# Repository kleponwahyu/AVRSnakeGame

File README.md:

8-bit Snake Game with AVR!
Complete with the schematic, board design, and the program!

The board design can be implemented for other games that uses low pixel count, for including tetris, car race and many more! (but no code yet...)

Note:
- The code is in C
- The board design and schematics are in EAGLE
- Already working as intended, but the pcb still need cleaning and can be shrinked.
- The Dot Matrix is in wrong angle, so physical and logical coordinates needed, and it takes memory space and clock. Will fix this for sure!

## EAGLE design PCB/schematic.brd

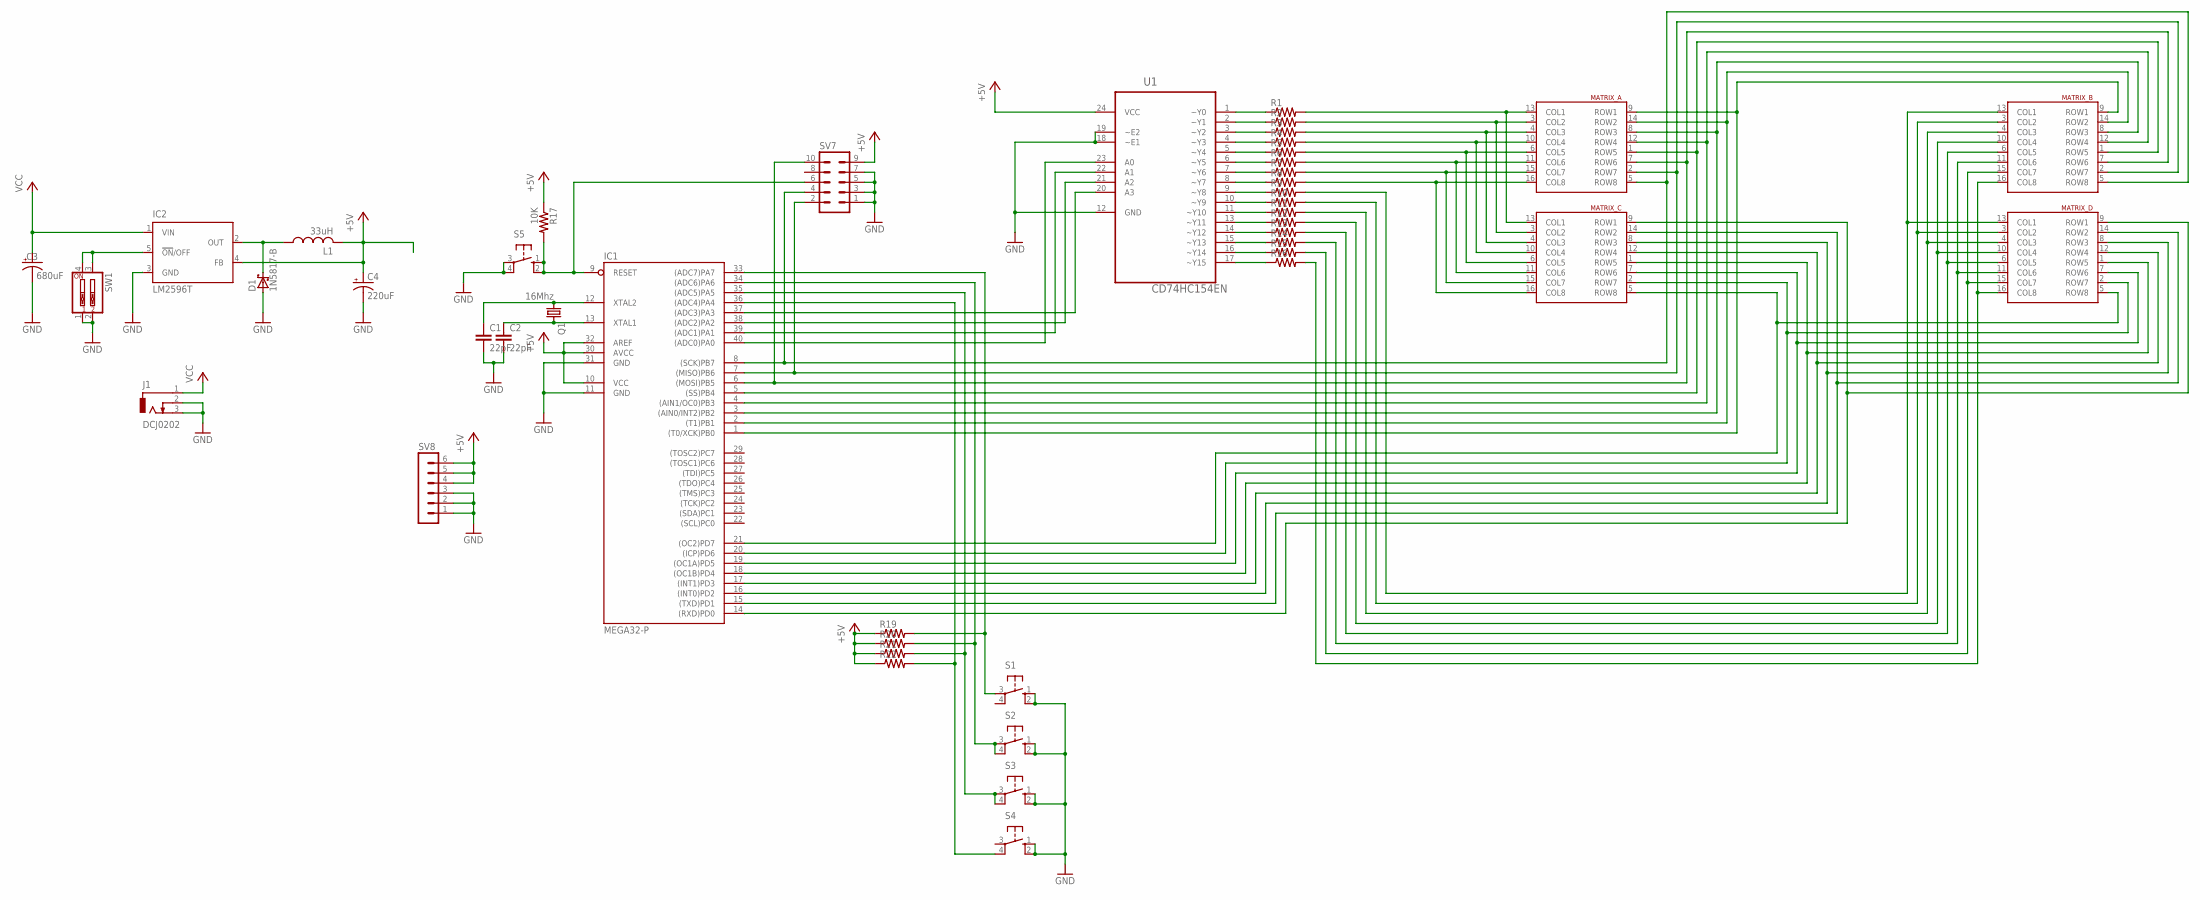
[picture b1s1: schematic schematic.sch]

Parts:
C1, C2: 22pF; C025-024X044
C3: 680uF; E3,5-8
C4: 220uF; E3,5-8
D1: 1N5817-B; DO41-7.6
IC1: MEGA32-P; DIL40
IC2: LM2596T; T05D
J1: DCJ0202
L1: 33uH; 0207/10
MATRIX_A: LED_8X8_MATRIXYGD2/A; MATRIX_8X8_38MM
MATRIX_B: LED_8X8_MATRIXYGD2/A; MATRIX_8X8_38MM
MATRIX_C: LED_8X8_MATRIXYGD2/A; MATRIX_8X8_38MM
MATRIX_D: LED_8X8_MATRIXYGD2/A; MATRIX_8X8_38MM
Q1: 16Mhz; HC49/S
R1, R2, R3, R4, R5, R6, R7, R8, R9, R10, R11, R12, R13, R14, R15, R16: R-US_0204/2V; 0204V
R17: 10K; 0204/7
R19, R20, R21, R22: R-US_0204/7; 0204/7
S1, S2, S3, S4, S5: 10-XX; B3F-10XX
SV7: MA05-2
SV8: MA06-1
SW1: SW_DIP-2; EDG-02
U1: CD74HC154EN; DIP254P762X508-24

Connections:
+5V: C4.+, IC1.10 (VCC), IC1.30 (AVCC), IC1.32 (AREF), IC2.4 (FB), L1.2, R17.1, R19.1, R20.1, R21.1, R22.1, SV7.9, SV8.4, SV8.5, SV8.6, U1.24 (VCC)
GND: C1.2, C2.2, C3.-, C4.-, D1.A, IC1.11 (GND), IC1.31 (GND), IC2.3 (GND), J1.2, J1.3, S1.1 (S), S1.2 (S1), S2.1 (S), S2.2 (S1), S3.1 (S), S3.2 (S1), S4.1 (S), S4.2 (S1), S5.3, S5.4 (P1), SV7.1, SV7.3, SV7.5, SV7.7, SV8.1, SV8.2, SV8.3, SW1.1, SW1.2, U1.12 (GND), U1.18 (~E1), U1.19 (~E2)
unnamed: R1.1, U1.1 (~Y0)
unnamed: R2.1, U1.2 (~Y1)
unnamed: R3.1, U1.3 (~Y2)
unnamed: R4.1, U1.4 (~Y3)
unnamed: R5.1, U1.5 (~Y4)
unnamed: R6.1, U1.6 (~Y5)
unnamed: R7.1, U1.7 (~Y6)
unnamed: R8.1, U1.8 (~Y7)
unnamed: R9.1, U1.9 (~Y8)
unnamed: R10.1, U1.10 (~Y9)
unnamed: R11.1, U1.11 (~Y10)
unnamed: R12.1, U1.13 (~Y11)
unnamed: R13.1, U1.14 (~Y12)
unnamed: R14.1, U1.15 (~Y13)
unnamed: R15.1, U1.16 (~Y14)
unnamed: R16.1, U1.17 (~Y15)
unnamed: MATRIX_A.13 (COL1), MATRIX_C.13 (COL1), R1.2
unnamed: MATRIX_A.3 (COL2), MATRIX_C.3 (COL2), R2.2
unnamed: MATRIX_A.4 (COL3), MATRIX_C.4 (COL3), R3.2
unnamed: MATRIX_A.10 (COL4), MATRIX_C.10 (COL4), R4.2
unnamed: MATRIX_A.6 (COL5), MATRIX_C.6 (COL5), R5.2
unnamed: MATRIX_A.11 (COL6), MATRIX_C.11 (COL6), R6.2
unnamed: MATRIX_A.15 (COL7), MATRIX_C.15 (COL7), R7.2
unnamed: MATRIX_A.16 (COL8), MATRIX_C.16 (COL8), R8.2
unnamed: IC1.7 ((MISO)PB6), MATRIX_A.2 (ROW7), MATRIX_B.2 (ROW7), SV7.2
unnamed: IC1.8 ((SCK)PB7), MATRIX_A.5 (ROW8), MATRIX_B.5 (ROW8), SV7.4
unnamed: IC1.5 ((SS)PB4), MATRIX_A.1 (ROW5), MATRIX_B.1 (ROW5)
unnamed: IC1.3 ((AIN0/INT2)PB2), MATRIX_A.8 (ROW3), MATRIX_B.8 (ROW3)
unnamed: IC1.1 ((T0/XCK)PB0), MATRIX_A.9 (ROW1), MATRIX_B.9 (ROW1)
unnamed: IC1.15 ((TXD)PD1), MATRIX_C.14 (ROW2), MATRIX_D.14 (ROW2)
unnamed: IC1.17 ((INT1)PD3), MATRIX_C.12 (ROW4), MATRIX_D.12 (ROW4)
unnamed: IC1.20 ((ICP)PD6), MATRIX_C.2 (ROW7), MATRIX_D.2 (ROW7)
unnamed: IC1.9 (RESET), R17.2, S5.1 (S), S5.2 (S1), SV7.6
unnamed: MATRIX_B.15 (COL7), MATRIX_D.15 (COL7), R15.2
unnamed: C2.1, IC1.13 (XTAL1), Q1.2
unnamed: MATRIX_B.6 (COL5), MATRIX_D.6 (COL5), R13.2
unnamed: C1.1, IC1.12 (XTAL2), Q1.1
unnamed: MATRIX_B.4 (COL3), MATRIX_D.4 (COL3), R11.2
unnamed: MATRIX_B.13 (COL1), MATRIX_D.13 (COL1), R9.2
unnamed: IC1.39 ((ADC1)PA1), U1.22 (A1)
unnamed: IC1.37 ((ADC3)PA3), U1.20 (A3)
unnamed: IC1.34 ((ADC6)PA6), R20.2, S2.3, S2.4 (P1)
unnamed: IC1.36 ((ADC4)PA4), R22.2, S4.4 (P1)
unnamed: MATRIX_B.3 (COL2), MATRIX_D.3 (COL2), R10.2
unnamed: IC1.2 ((T1)PB1), MATRIX_A.14 (ROW2), MATRIX_B.14 (ROW2)
unnamed: MATRIX_B.10 (COL4), MATRIX_D.10 (COL4), R12.2
unnamed: MATRIX_B.11 (COL6), MATRIX_D.11 (COL6), R14.2
unnamed: IC1.4 ((AIN1/OC0)PB3), MATRIX_A.12 (ROW4), MATRIX_B.12 (ROW4)
unnamed: MATRIX_B.16 (COL8), MATRIX_D.16 (COL8), R16.2
unnamed: IC1.6 ((MOSI)PB5), MATRIX_A.7 (ROW6), MATRIX_B.7 (ROW6), SV7.10
unnamed: IC1.14 ((RXD)PD0), MATRIX_C.9 (ROW1), MATRIX_D.9 (ROW1)
unnamed: IC1.16 ((INT0)PD2), MATRIX_C.8 (ROW3), MATRIX_D.8 (ROW3)
unnamed: IC1.18 ((OC1B)PD4), MATRIX_C.1 (ROW5), MATRIX_D.1 (ROW5)
unnamed: IC1.19 ((OC1A)PD5), MATRIX_C.7 (ROW6), MATRIX_D.7 (ROW6)
unnamed: IC1.21 ((OC2)PD7), MATRIX_C.5 (ROW8), MATRIX_D.5 (ROW8)
unnamed: IC1.35 ((ADC5)PA5), R21.2, S3.3, S3.4 (P1)
unnamed: IC1.33 ((ADC7)PA7), R19.2, S1.3
unnamed: IC1.40 ((ADC0)PA0), U1.23 (A0)
unnamed: IC1.38 ((ADC2)PA2), U1.21 (A2)
unnamed: D1.C, IC2.2 (OUT), L1.1
unnamed: IC2.5 (!ON!/OFF), SW1.3, SW1.4
VCC: C3.+, IC2.1 (VIN), J1.1

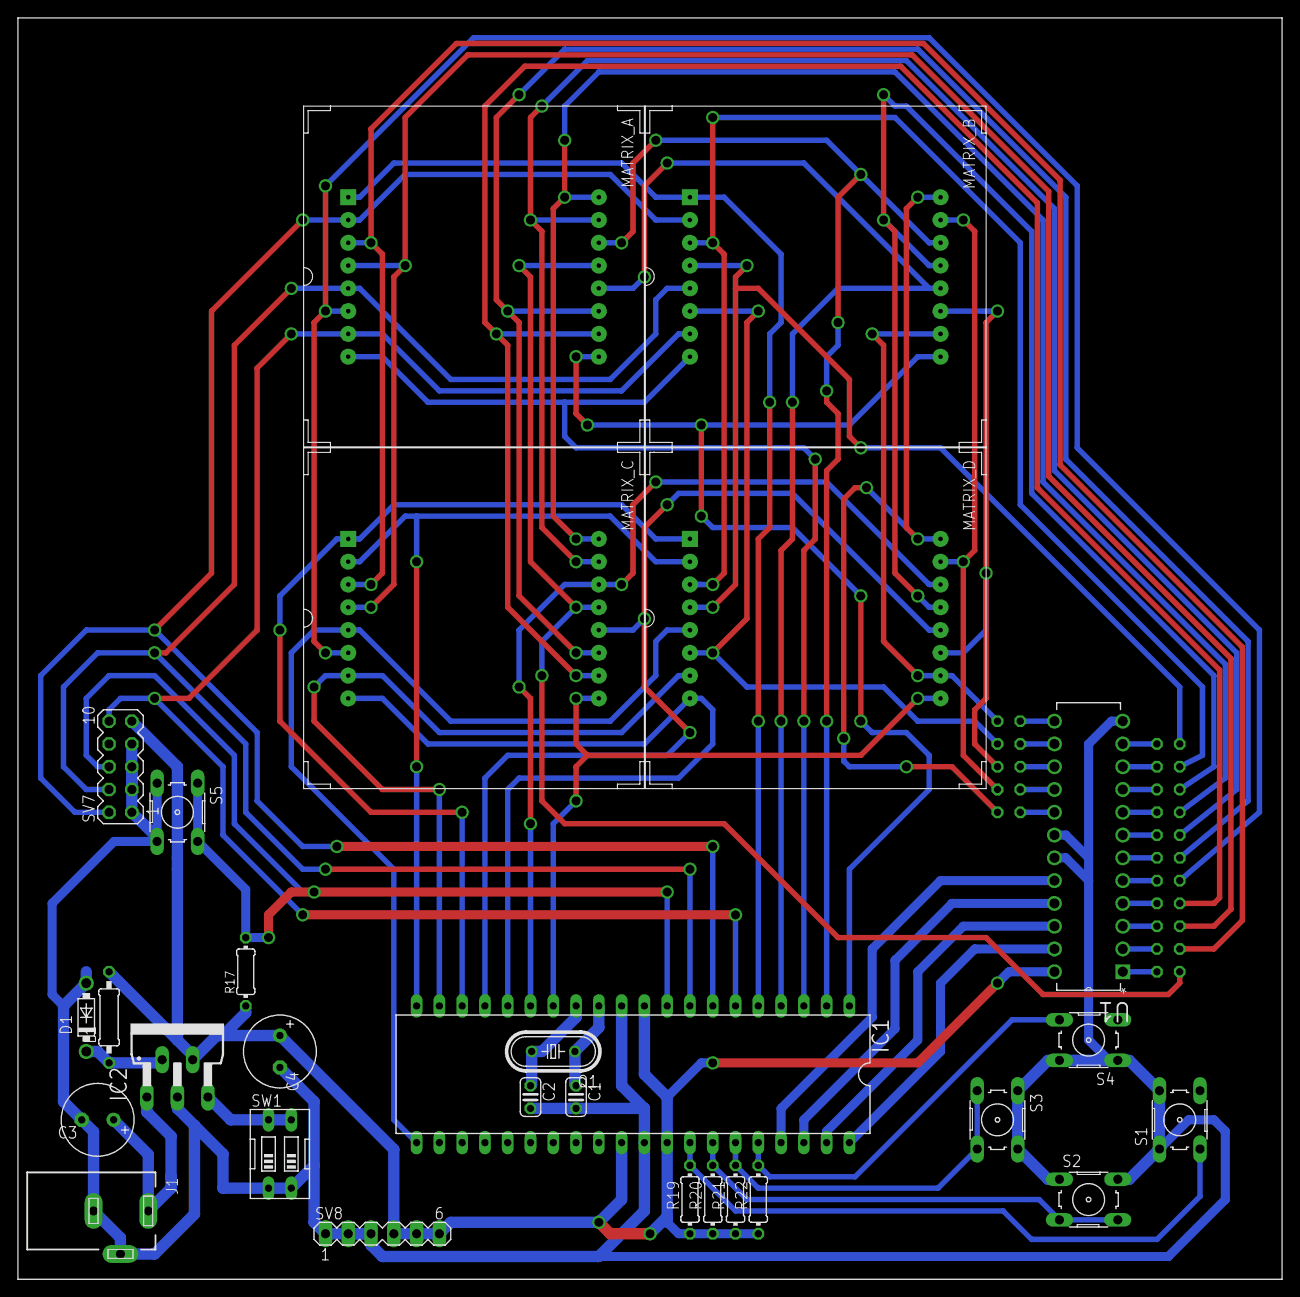
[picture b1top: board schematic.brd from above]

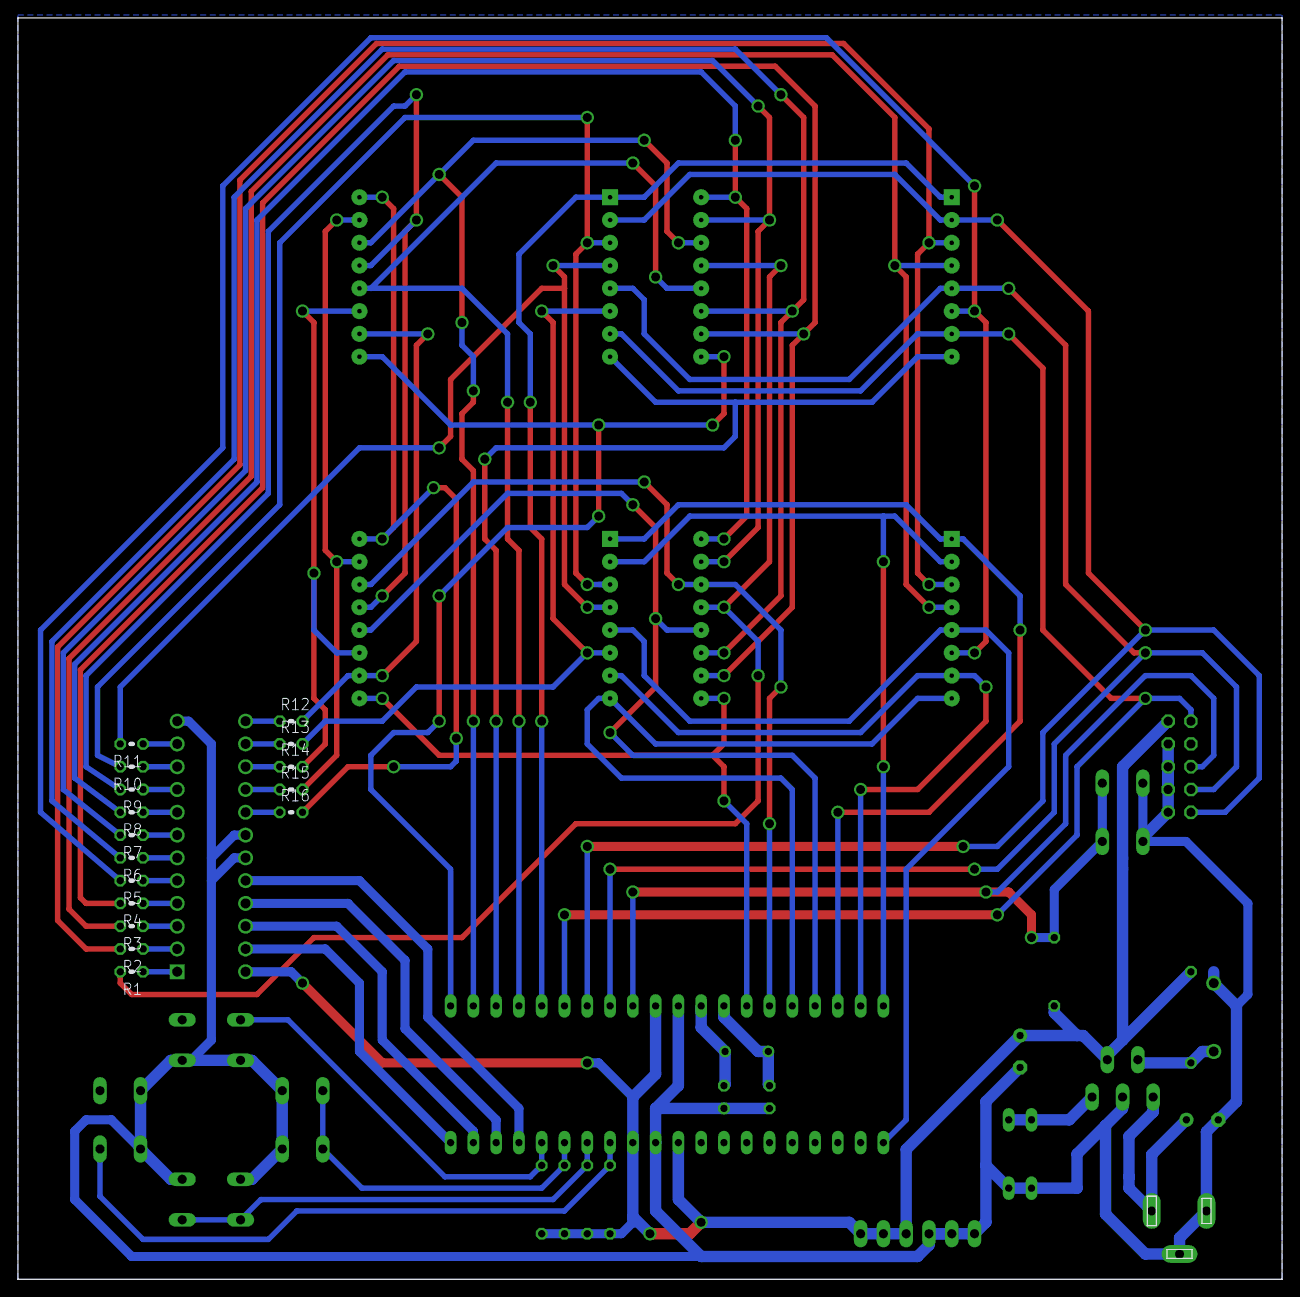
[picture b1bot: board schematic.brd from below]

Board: 2 copper layers, 140.9 x 140.6 mm, 44 parts (16 on the bottom side), 64 nets.

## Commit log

2018-12-03 First commit, already tested but the PCB still need cleaning
2018-12-03 Adding README.md
2018-12-03 Edit README.md
2018-12-03 Rename schematic.brd to board.brd
